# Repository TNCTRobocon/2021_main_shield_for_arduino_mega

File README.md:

# 2021_main_shield_for_arduino_mega
2021年用本ロボメインシールド　言われないとpullしないので変更したら言ってください
なんかリポジトリmainじゃなくてmasterに入れてもうた許してなんもしないけど

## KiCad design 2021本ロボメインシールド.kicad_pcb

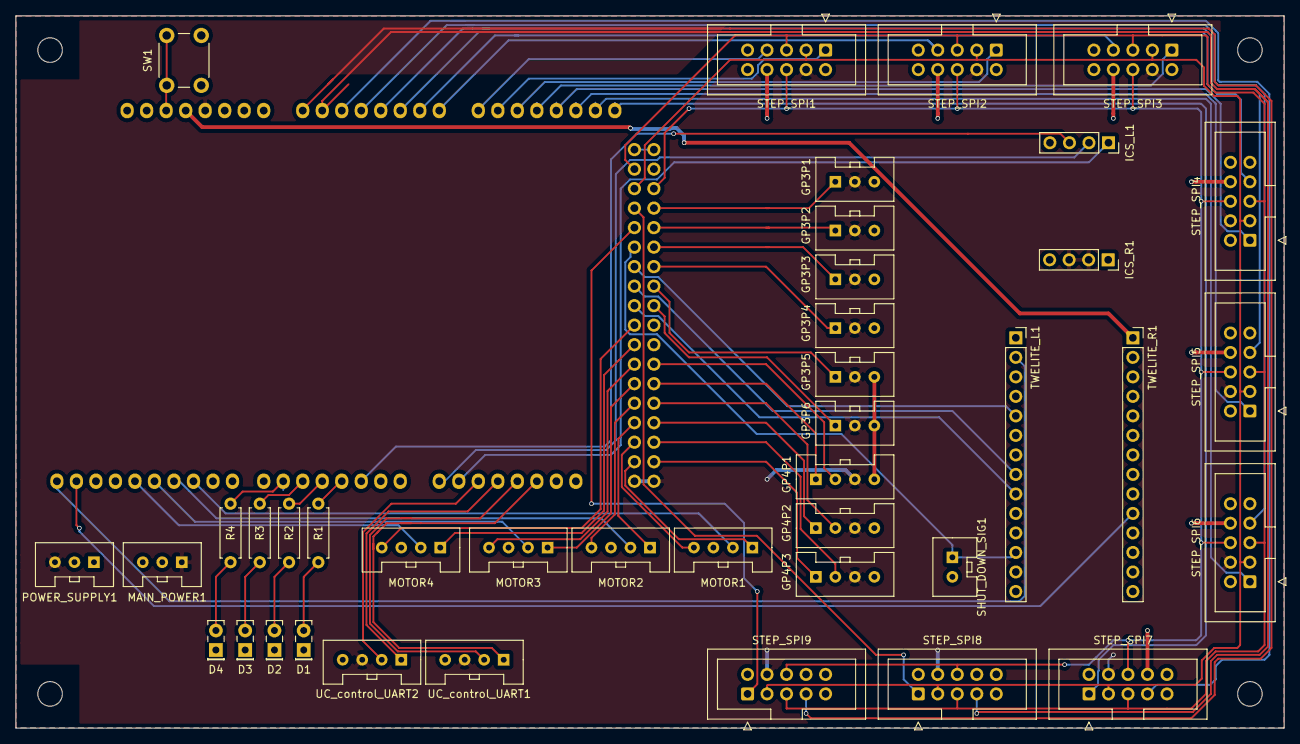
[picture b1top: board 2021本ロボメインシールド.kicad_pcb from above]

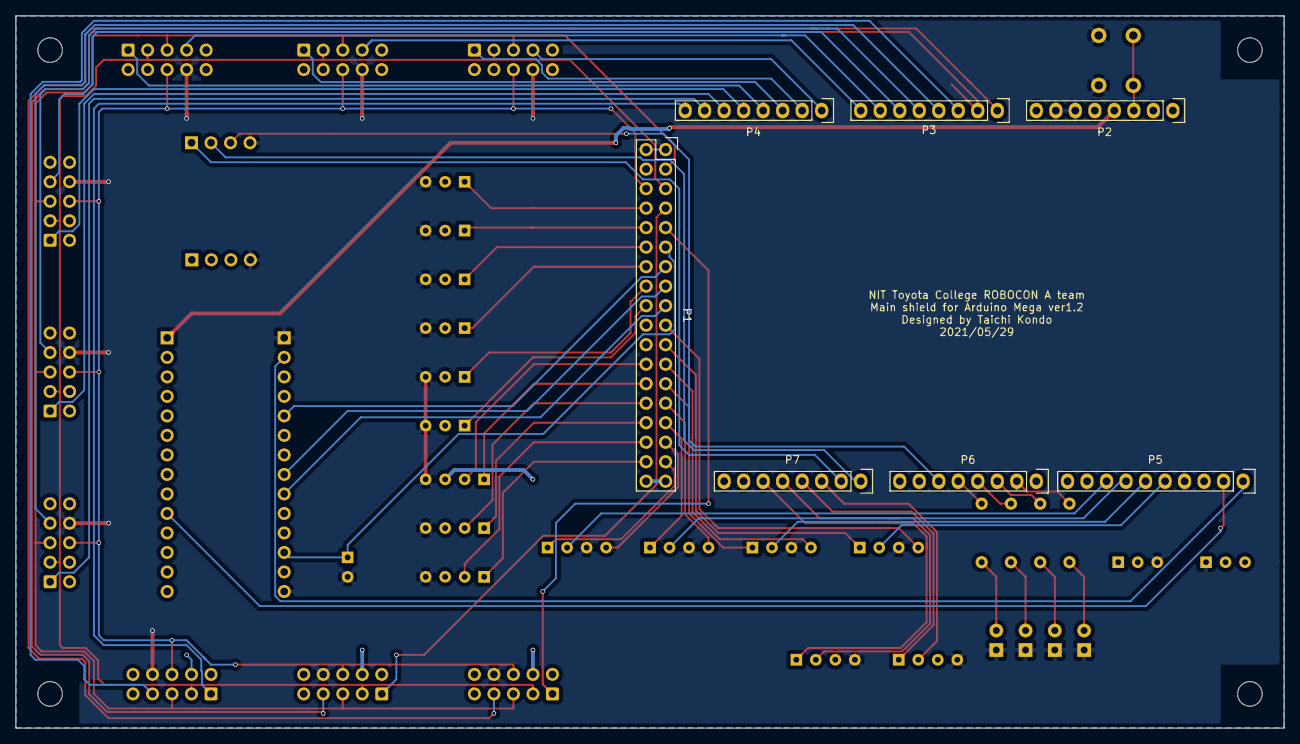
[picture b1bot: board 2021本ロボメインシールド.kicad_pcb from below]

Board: 2 copper layers, 165.1 x 92.7 mm, 47 parts (7 on the bottom side), 70 nets.

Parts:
D1, D2, D3, D4: LED; LED_Rectangular_W5.0mm_H2.0mm
GP3P1, GP3P2, GP3P3, GP3P4, GP3P5, GP3P6: Conn_01x03; XA_03
GP4P1, GP4P2, GP4P3: Conn_01x04; XA_04
ICS_L1: Conn_01x04; PinSocket_1x04_P2.54mm_Vertical
ICS_R1: Conn_01x04; PinSocket_1x04_P2.54mm_Vertical
MAIN_POWER1: Conn_01x03; XA_03
MOTOR1, MOTOR2, MOTOR3, MOTOR4: Conn_01x04; XA_04
P1: Digital; Socket_Strip_Arduino_2x18
P2: Power; Socket_Strip_Arduino_1x08
P3, P4: Analog; Socket_Strip_Arduino_1x08
P5: PWM; Socket_Strip_Arduino_1x10
P6: PWM; Socket_Strip_Arduino_1x08
P7: Communication; Socket_Strip_Arduino_1x08
POWER_SUPPLY1: Conn_01x03; XA_03
R1, R2, R3, R4: R; R_Axial_DIN0207_L6.3mm_D2.5mm_P7.62mm_Horizontal
SHUT_DOWN_SIG1: Conn_01x02; XA_02
STEP_SPI1, STEP_SPI2, STEP_SPI3, STEP_SPI4, STEP_SPI5, STEP_SPI6, STEP_SPI7, STEP_SPI8, STEP_SPI9: Conn_02x05_Odd_Even; IDC-Header_2x05_P2.54mm_Vertical
SW1: SW_Push; SW_PUSH_6mm
TWELITE_L1: Conn_01x14; PinSocket_1x14_P2.54mm_Vertical
TWELITE_R1: Conn_01x14; PinSocket_1x14_P2.54mm_Vertical
UC_control_UART1, UC_control_UART2: Conn_01x04; XA_04

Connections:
+3V3: P2.4, TWELITE_R1.1
+5V: GP3P1.2, GP3P2.2, GP3P3.2, GP3P4.2, GP3P5.2, GP3P6.2, GP4P1.3, GP4P2.3, GP4P3.3, ICS_R1.2, ICS_R1.3, MAIN_POWER1.1, P1.35, P1.36, P2.5, POWER_SUPPLY1.3, STEP_SPI1.4, STEP_SPI2.4, STEP_SPI3.4, STEP_SPI4.4, STEP_SPI5.4, STEP_SPI6.4, STEP_SPI7.4, STEP_SPI8.4, STEP_SPI9.4, UC_control_UART1.3, UC_control_UART2.3
BUSY1: P4.2, STEP_SPI1.1
BUSY2: P4.3, STEP_SPI2.1
BUSY3: P4.4, STEP_SPI3.1
BUSY4: P4.5, STEP_SPI4.1
BUSY5: P4.6, STEP_SPI5.1
BUSY6: P4.7, STEP_SPI6.1
BUSY7: P4.8, STEP_SPI7.1
BUSY8: P1.7, STEP_SPI8.1
BUSY9: P1.9, STEP_SPI9.1
DO1: P1.13, TWELITE_L1.5
DO2: P1.15, TWELITE_L1.8
DO3: P1.17, TWELITE_L1.9
EN_IN: ICS_L1.3, P6.6
GND: D1.1, D2.1, D3.1, D4.1, GP3P1.3, GP3P2.3, GP3P3.3, GP3P4.3, GP3P5.3, GP3P6.3, GP4P1.4, GP4P2.4, GP4P3.4, ICS_L1.4, ICS_R1.4, MAIN_POWER1.3, MOTOR1.3, MOTOR2.3, MOTOR3.3, MOTOR4.3, P1.1, P1.2, P2.6, P2.7, P5.4, POWER_SUPPLY1.1, SHUT_DOWN_SIG1.2, STEP_SPI1.8, STEP_SPI2.8, STEP_SPI3.8, STEP_SPI4.8, STEP_SPI5.8, STEP_SPI6.8, STEP_SPI7.8, STEP_SPI8.8, STEP_SPI9.8, SW1.1, TWELITE_L1.1, TWELITE_L1.14, UC_control_UART1.4, UC_control_UART2.4
GP3P1_1: GP3P1.1, P1.8
GP3P2_1: GP3P2.1, P1.10
GP3P3_1: GP3P3.1, P1.12
GP3P4_1: GP3P4.1, P1.14
GP3P5_1: GP3P5.1, P1.16
GP3P6_1: GP3P6.1, P1.18
GP4P1_1: GP4P1.1, P1.26
GP4P1_2: GP4P1.2, P1.24
GP4P2_1: GP4P2.1, P1.30
GP4P2_2: GP4P2.2, P1.28
GP4P3_1: GP4P3.1, P1.34
GP4P3_2: GP4P3.2, P1.32
IN_A1: MOTOR1.1, P1.33
IN_A2: MOTOR2.1, P1.29
IN_A3: MOTOR3.1, P1.25
IN_A4: MOTOR4.1, P1.21
IN_B1: MOTOR1.4, P1.31
IN_B2: MOTOR2.4, P1.27
IN_B3: MOTOR3.4, P1.23
IN_B4: MOTOR4.4, P1.19
LED1: P6.5, R1.1
LED2: P6.4, R2.1
LED3: P6.3, R3.1
LED4: P6.2, R4.1
MISO: P1.5, STEP_SPI1.3, STEP_SPI2.3, STEP_SPI3.3, STEP_SPI4.3, STEP_SPI5.3, STEP_SPI6.3, STEP_SPI7.3, STEP_SPI8.3, STEP_SPI9.3
MOSI: P1.6, STEP_SPI1.6, STEP_SPI2.6, STEP_SPI3.6, STEP_SPI4.6, STEP_SPI5.6, STEP_SPI6.6, STEP_SPI7.6, STEP_SPI8.6, STEP_SPI9.6
MPWM1: MOTOR1.2, P5.8
MPWM2: MOTOR2.2, P5.7
MPWM3: MOTOR3.2, P5.6
MPWM4: MOTOR4.2, P5.5
unnamed: D1.2, R1.2
unnamed: D2.2, R2.2
unnamed: D3.2, R3.2
unnamed: D4.2, R4.2
RESET: P2.3, SW1.2
RX1: P7.6, UC_control_UART1.1
RX2: P7.4, UC_control_UART2.1
RX3: ICS_L1.1, P7.2
SCK: P1.3, STEP_SPI1.5, STEP_SPI2.5, STEP_SPI3.5, STEP_SPI4.5, STEP_SPI5.5, STEP_SPI6.5, STEP_SPI7.5, STEP_SPI8.5, STEP_SPI9.5
SCL: P5.1, TWELITE_L1.2
SDA: P5.2, TWELITE_R1.10
SHUT_DOWM_SIG: P1.11, SHUT_DOWN_SIG1.1, TWELITE_L1.12
SS1: P4.1, STEP_SPI1.7
SS2: P3.8, STEP_SPI2.7
SS3: P3.7, STEP_SPI3.7
SS4: P3.6, STEP_SPI4.7
SS5: P3.5, STEP_SPI5.7
SS6: P3.4, STEP_SPI6.7
SS7: P3.3, STEP_SPI7.7
SS8: P3.2, STEP_SPI8.7
SS9: P3.1, STEP_SPI9.7
TX1: P7.5, UC_control_UART1.2
TX2: P7.3, UC_control_UART2.2
TX3: ICS_L1.2, P7.1

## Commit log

2021-06-27 ver1.0
2021-06-28 ver1.2
2021-06-29 ver1.3 stepping10->9
